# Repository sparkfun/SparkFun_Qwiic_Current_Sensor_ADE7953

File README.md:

The [SparkFun Non-Invasive Current Sensor - ADE7953 (Qwiic)](https://www.sparkfun.com/sparkfun-non-invasive-current-sensor-ade7953-qwiic.html) is a dual-channel, non-invasive current measurement breakout built around the ADE7953 energy metering IC from Analog Devices. Using inexpensive SCT-013 split-core current transformers (CT clamps), you can measure AC current on up to two channels without ever breaking a wire. The board accepts CT input through a standard 3.5mm TRRS audio jack or through the A+/A- and B+/B- terminal connections, giving you flexibility for both quick prototyping and permanent installations.

Designed for our [Qwiic ecosystem](https://www.sparkfun.com/qwiic), the ADE7953 handles all of the signal conditioning, sampling, and power calculations on-chip, delivering calibrated current readings over I2C so your host microcontroller can stay focused on application logic. Whether you are building a home energy monitor, an industrial equipment dashboard, or a smart breaker panel, this board gives you metering-grade measurements in a compact, breadboard-friendly package.

## Repository Contents

* **/docs** - Documentation files for GitHub pages
* **/Documents** - Datasheets, additional product information
* **/Hardware** - KiCad design files (.kicad_sch, .kicad_pcb)
* **/Production** - Production panel files

## Documentation

* **[Library](https://github.com/sparkfun/SparkFun_ADE7953_Arduino_Library)** - Arduino library for the SparkFun Non-Invasive Current Sensor - ADE7953 (Qwiic).
* **[Hookup Guide](https://docs.sparkfun.com/SparkFun_Qwiic_Current_Sensor_ADE7953/)** - Basic hookup guide for the SparkFun Non-Invasive Current Sensor - ADE7953 (Qwiic).

## Product Versions

* **[SEN-31409](https://www.sparkfun.com/sparkfun-non-invasive-current-sensor-ade7953-qwiic.html)** - Initial release of the SparkFun Qwiic Current Sensor - ADE7953.

## License Information

This product is _**open source**_!

Please review the LICENSE.md file for license information.

If you have any questions or concerns about licensing, please contact technical support on our [SparkFun forums](https://forum.sparkfun.com/viewforum.php?f=152).

Distributed as-is; no warranty is given.

_- Your friends at SparkFun._

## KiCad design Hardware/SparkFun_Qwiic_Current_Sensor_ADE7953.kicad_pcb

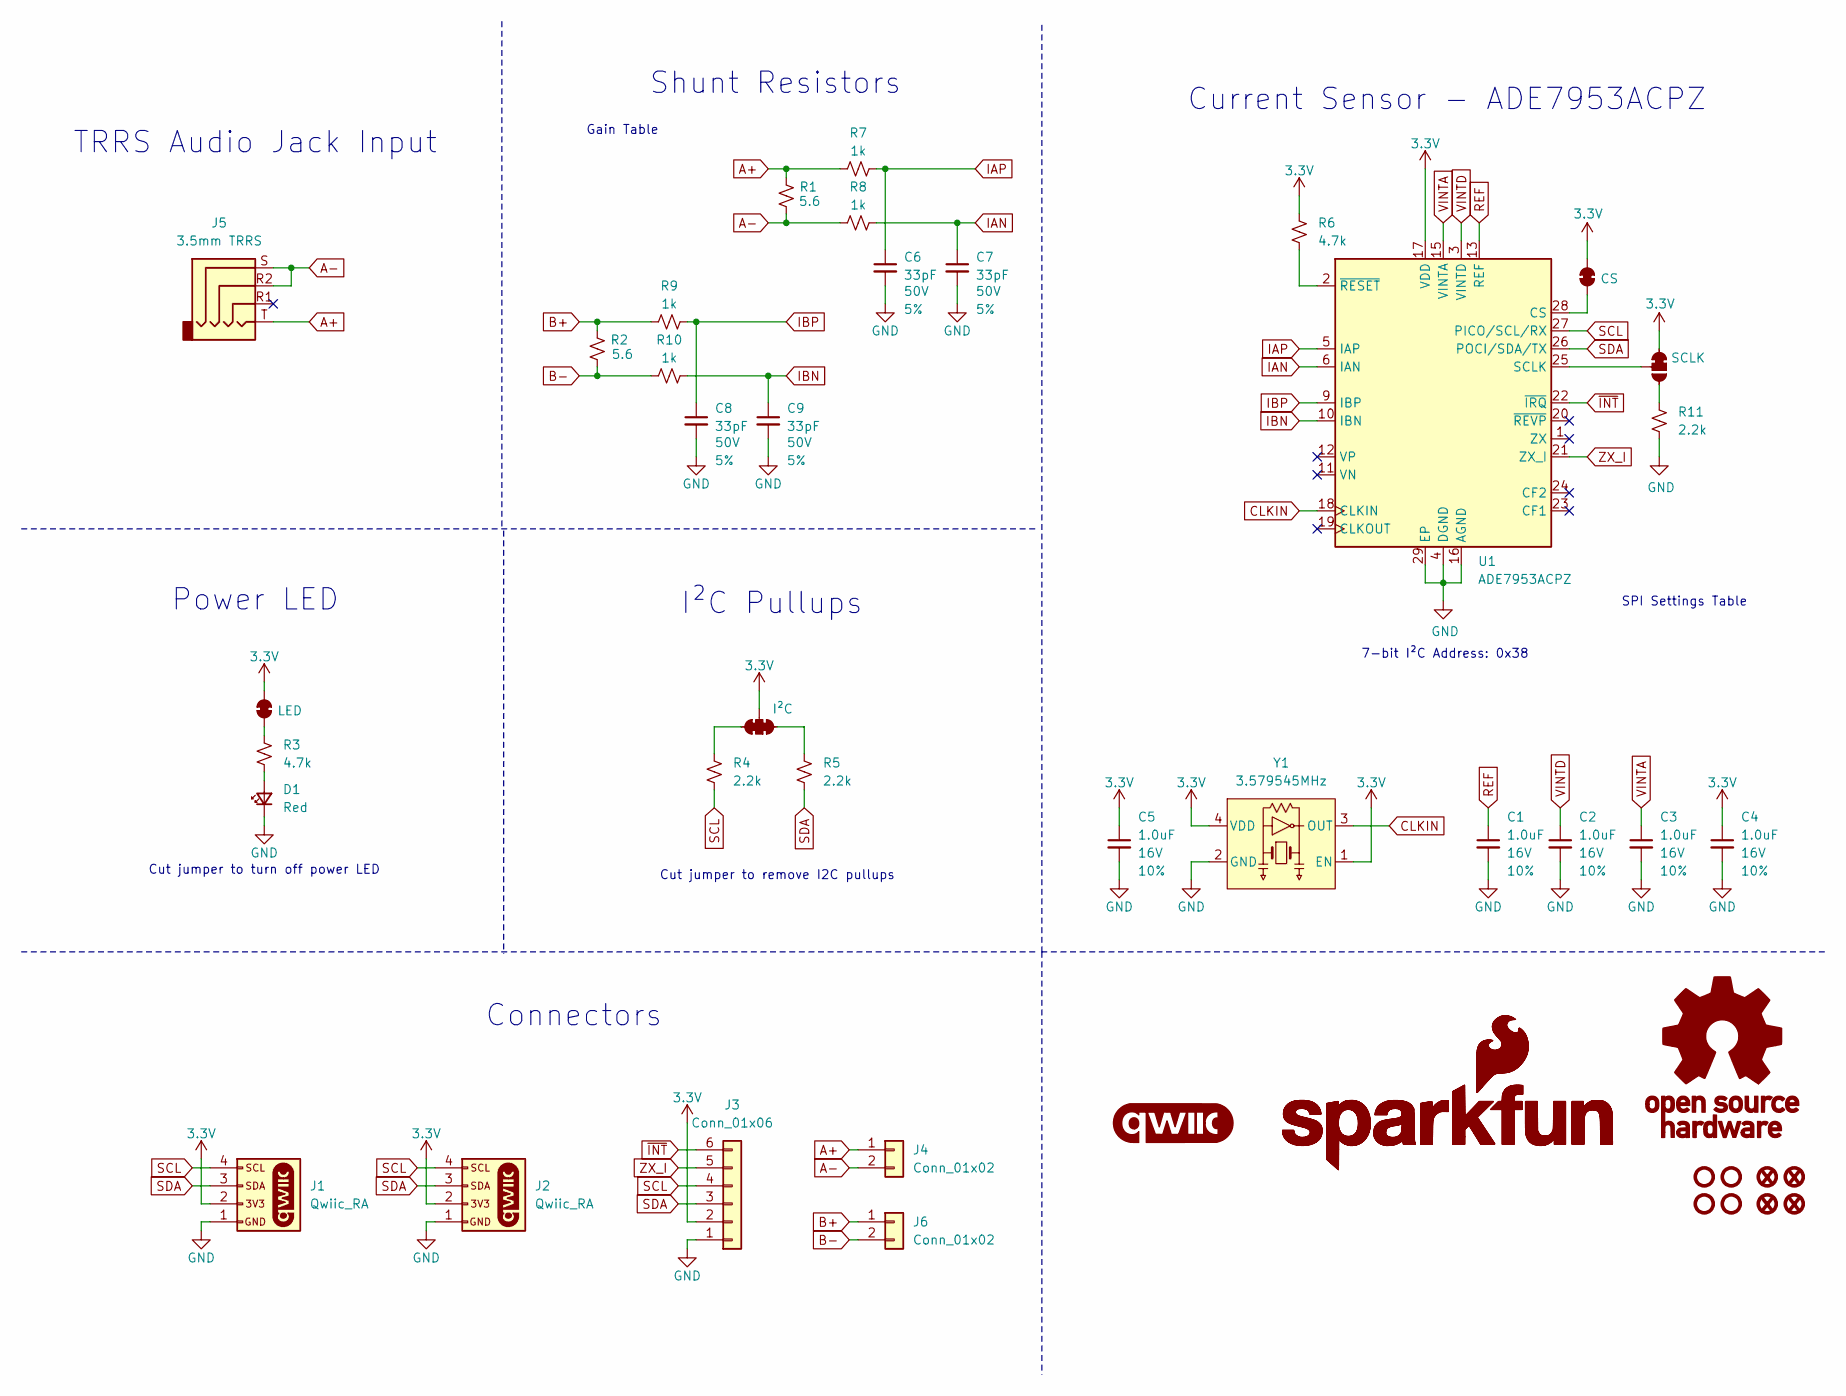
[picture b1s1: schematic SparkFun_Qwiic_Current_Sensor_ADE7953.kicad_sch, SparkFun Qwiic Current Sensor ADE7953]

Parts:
C1, C2, C3, C4, C5: 1.0uF; C_0402_1005Metric; Voltage 16V; Tolerance 10%
C6, C7, C8, C9: 33pF; C_0402_1005Metric; Voltage 50V; Tolerance 5%
D1: Red; LED_0603_1608Metric_Red
FID1, FID2, FID3, FID4: Fiducial_0.5mm; Fiducial_0.5mm_Mask1mm
G1: qwiic_Logo
G2: SparkFun_Logo; SparkFun_Logo_8mm
G3: SparkFun_Logo
G4: OSHW_Logo; Creative_Commons_License
J1, J2: Qwiic_RA; JST_1x04_P1.0mm_Horizontal_SMD
J3: Conn_01x06; 1x06_P2.54mm
J4, J6: Conn_01x02; 1x02_P2.54mm
J5: 3.5mm TRRS; Audio_Jack_3.5mm_TRRS_SMD_RA
JP1: LED; Jumper_2_NC_Trace
JP2: I²C; Jumper_3_NC-2_Trace
JP3: SCLK; Jumper_3_NC-1_Trace
JP4: CS; Jumper_2_NC_Trace
R1, R2: 5.6; R_0603_1608Metric
R3, R6: 4.7k; R_0603_1608Metric
R4, R5, R11: 2.2k; R_0402_1005Metric
R7, R8, R9, R10: 1k; R_0402_1005Metric
ST1, ST2, ST3, ST4: Standoff
U1: ADE7953ACPZ; QFN-28-1EP_4x4_5mmx5mm; Manufacturer_Part_Number ADE7953ACPZ; Mouser Part Number 584-ADE7953ACPZ
Y1: 3.579545MHz; Crystal_SMD_3.2x2.5mm

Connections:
3.3V: C4.1, C5.1, J1.2, J2.2, J3.2, JP1.2 (B), JP2.2 (B), JP3.1 (A), JP4.2 (B), R6.2, U1.7 (PULL_HIGH_1), U1.8 (PULL_HIGH_2), U1.17 (VDD), Y1.1 (EN), Y1.4 (VDD)
A+: J4.1, J5.T, R1.2, R7.1
A-: J4.2, J5.R2, J5.S, R1.1, R8.1
B+: J6.1, R2.2, R9.1
B-: J6.2, R2.1, R10.1
CLKIN: U1.18 (CLKIN), Y1.3 (OUT)
GND: C1.2, C2.2, C3.2, C4.2, C5.2, C6.2, C7.2, C8.2, C9.2, D1.1 (K), J1.1, J2.1, J3.1, R11.1, U1.4 (DGND), U1.14 (PULL_LOW), U1.16 (AGND), U1.29 (EP), Y1.2 (GND)
IAN: C7.1, R8.2, U1.6 (IAN)
IAP: C6.1, R7.2, U1.5 (IAP)
IBN: C9.1, R10.2, U1.10 (IBN)
IBP: C8.1, R9.2, U1.9 (IBP)
unnamed: D1.2 (A), R3.1
unnamed: JP1.1 (A), R3.2
unnamed: JP2.1 (A), R5.2
unnamed: JP2.3 (C), R4.2
unnamed: JP3.2 (B), U1.25 (SCLK)
unnamed: JP3.3 (C), R11.2
unnamed: JP4.1 (A), U1.28 (CS)
unnamed: R6.1, U1.2 (~RESET)
REF: C1.1, U1.13 (REF)
SCL: J1.4, J2.4, J3.4, R4.1, U1.27 (PICO/SCL/RX)
SDA: J1.3, J2.3, J3.3, R5.1, U1.26 (POCI/SDA/TX)
VINTA: C3.1, U1.15 (VINTA)
VINTD: C2.1, U1.3 (VINTD)
ZX_I: J3.5, U1.21 (ZX_I)
~INT: J3.6, U1.22 (~IRQ)

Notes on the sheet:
SPI Settings Table
Current Sensor - ADE7953ACPZ
Shunt Resistors
TRRS Audio Jack Input
7-bit I²C Address: 0x38
Cut jumper to turn off power LED
Power LED
Cut jumper to remove I2C pullups
Gain Table
Connectors
I²C Pullups

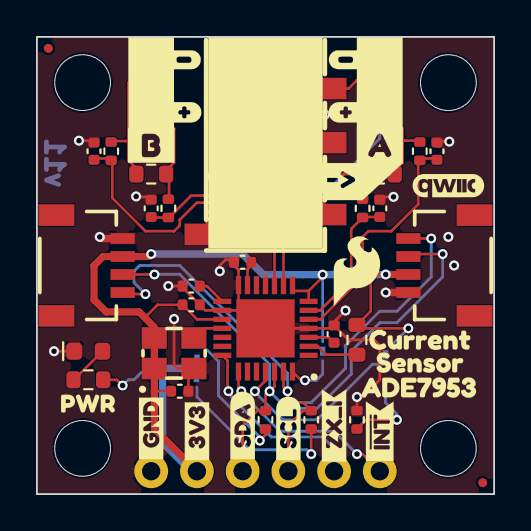
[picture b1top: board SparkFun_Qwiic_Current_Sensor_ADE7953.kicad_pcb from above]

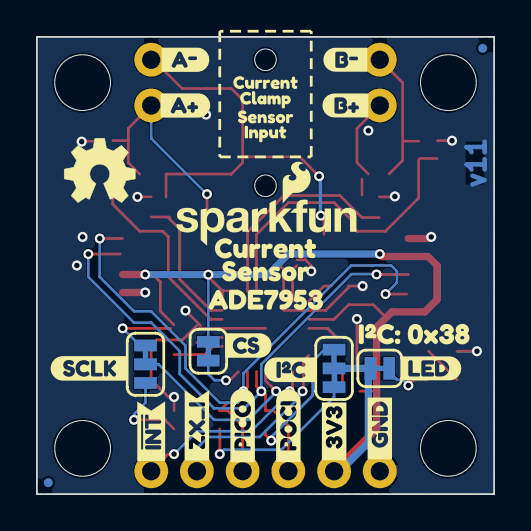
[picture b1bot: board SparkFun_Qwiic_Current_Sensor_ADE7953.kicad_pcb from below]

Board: 2 copper layers, 25.4 x 25.4 mm, 83 parts (29 on the bottom side), 26 nets.

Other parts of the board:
Ref**: Val**; OSHW_Logo_4mm
kibuzzard-6A8F671A: G***; kibuzzard-6A8F671A
kibuzzard-6A8F6918: G***; kibuzzard-6A8F6918
kibuzzard-6A8F6922: G***; kibuzzard-6A8F6922
kibuzzard-6A3051E6: G***; kibuzzard-6A3051E6
kibuzzard-69F8C340: G***; kibuzzard-69F8C340
kibuzzard-69F8FC1F, kibuzzard-69F8FC1F#2: G***; kibuzzard-69F8FC1F
kibuzzard-69F8FC56, kibuzzard-69F8FC56#2: G***; kibuzzard-69F8FC56
kibuzzard-69F8FCF4: G***; kibuzzard-69F8FCF4
kibuzzard-69F8FD80: G***; kibuzzard-69F8FD80
kibuzzard-69FA12A1, kibuzzard-69FA12A1#2: G***; kibuzzard-69FA12A1
kibuzzard-69FA12DB: G***; kibuzzard-69FA12DB
kibuzzard-69FA13A0: G***; kibuzzard-69FA13A0
kibuzzard-69FA13AB: G***; kibuzzard-69FA13AB
kibuzzard-69FA13C4: G***; kibuzzard-69FA13C4
kibuzzard-69FA13D5: G***; kibuzzard-69FA13D5
kibuzzard-69FA128B, kibuzzard-69FA128B#2: G***; kibuzzard-69FA128B
kibuzzard-69FA1293, kibuzzard-69FA1293#2: G***; kibuzzard-69FA1293
kibuzzard-69FCD097: G***; kibuzzard-69FCD097
kibuzzard-69FCDE2E: G***; kibuzzard-69FCDE2E
kibuzzard-69FD0DBC: G***; kibuzzard-69FD0DBC
kibuzzard-69FD0DD3: G***; kibuzzard-69FD0DD3
kibuzzard-69FD0DDA: G***; kibuzzard-69FD0DDA
kibuzzard-69FD0F08: G***; kibuzzard-69FD0F08
kibuzzard-69FD10A0: G***; kibuzzard-69FD10A0
kibuzzard-69FD10AE: G***; kibuzzard-69FD10AE
kibuzzard-69FD1032: G***; kibuzzard-69FD1032
kibuzzard-69FD1060: G***; kibuzzard-69FD1060
kibuzzard-689A66E2: G***; kibuzzard-689A66E2
kibuzzard-689A66E9: G***; kibuzzard-689A66E9
kibuzzard-689A66EE: G***; kibuzzard-689A66EE
kibuzzard-689A66F4: G***; kibuzzard-689A66F4
kibuzzard-689A642E: G***; kibuzzard-689A642E
kibuzzard-689A6721: G***; kibuzzard-689A6721
kibuzzard-689A6728: G***; kibuzzard-689A6728
kibuzzard-689A6796: G***; kibuzzard-689A6796

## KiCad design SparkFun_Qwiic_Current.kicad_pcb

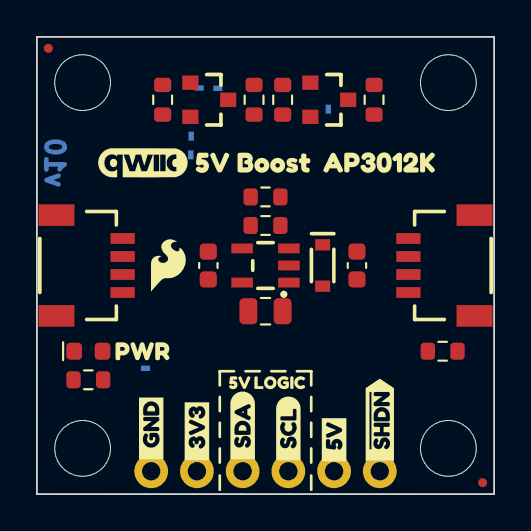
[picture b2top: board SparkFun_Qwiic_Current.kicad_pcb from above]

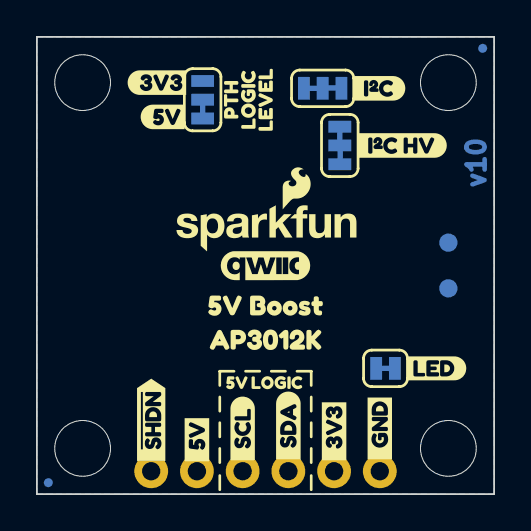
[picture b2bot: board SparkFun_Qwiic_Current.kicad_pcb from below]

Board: 2 copper layers, 25.4 x 25.4 mm, 63 parts (26 on the bottom side), 17 nets, no tracks yet.

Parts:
C1, C2: 1.0uF; C_0603_1608Metric
D1: Red; LED_0603_1608Metric_Red
D2: PMEG4005EJ; SOD-323
FID1, FID2, FID3, FID4: Fiducial_0.5mm; Fiducial_0.5mm_Mask1mm
G4: OSHW_Logo; Creative_Commons_License
J1, J2: Qwiic_RA; JST_1x04_P1.0mm_Horizontal_SMD
J3: Conn_01x06; 1x06_P2.54mm
JP1: LED; Jumper_2_NC_Trace
JP2: I2C; Jumper_3_NC-2_Trace
JP3: LOGIC; Jumper_3_NC-1_Trace
JP4: I2C HV; Jumper_3_NC-2_Trace
L1: 10uH; C_0805_2012Metric
Q1, Q2: BSS138; SOT23-3
R1, R6: 100k; R_0603_1608Metric
R2: 33k; R_0603_1608Metric
R3: 4.7k; R_0603_1608Metric
R4, R5, R7, R8: 2.2k; R_0603_1608Metric
ST1, ST2, ST3, ST4: Standoff
TP1, TP2: 1.0mm; TestPoint-1.0mm
U5: AP3012; SOT23-5
kibuzzard-689A64A8: G***; kibuzzard-689A64A8
kibuzzard-689A66E2: G***; kibuzzard-689A66E2
kibuzzard-689A66E9: G***; kibuzzard-689A66E9
kibuzzard-689A66EE: G***; kibuzzard-689A66EE
kibuzzard-689A66F4: G***; kibuzzard-689A66F4
kibuzzard-689A66F9: G***; kibuzzard-689A66F9
kibuzzard-689A66FE: G***; kibuzzard-689A66FE
kibuzzard-689A642E: G***; kibuzzard-689A642E
kibuzzard-689A644B: G***; kibuzzard-689A644B
kibuzzard-689A648B: G***; kibuzzard-689A648B
kibuzzard-689A649F: G***; kibuzzard-689A649F
kibuzzard-689A670C: G***; kibuzzard-689A670C
kibuzzard-689A676B: G***; kibuzzard-689A676B
kibuzzard-689A6411: G***; kibuzzard-689A6411
kibuzzard-689A6418: G***; kibuzzard-689A6418
kibuzzard-689A6454: G***; kibuzzard-689A6454
kibuzzard-689A6479: G***; kibuzzard-689A6479
kibuzzard-689A6481: G***; kibuzzard-689A6481
kibuzzard-689A6494: G***; kibuzzard-689A6494
kibuzzard-689A6706: G***; kibuzzard-689A6706
kibuzzard-689A6711: G***; kibuzzard-689A6711
kibuzzard-689A6718: G***; kibuzzard-689A6718
kibuzzard-689A6721: G***; kibuzzard-689A6721
kibuzzard-689A6728: G***; kibuzzard-689A6728
kibuzzard-689A6759: G***; kibuzzard-689A6759
kibuzzard-689A6762: G***; kibuzzard-689A6762
kibuzzard-689A6771: G***; kibuzzard-689A6771
kibuzzard-689A6775: G***; kibuzzard-689A6775
kibuzzard-689A6796: G***; kibuzzard-689A6796

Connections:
3.3V: C1.1, J1.2, J2.2, J3.2, JP1.2 (B), JP2.2 (B), JP3.3 (C), L1.1, Q1.1 (G), Q2.1 (G), R6.2, U5.5 (IN)
5V: C2.1, D2.1 (K), J3.5, JP3.1 (A), R1.2
GND: C1.2, C2.2, D1.1 (K), J1.1, J2.1, J3.1, R2.2, U5.2 (GND)
HV_SCL: J3.4, Q1.3 (D), R8.2
HV_SDA: J3.3, Q2.3 (D), R7.2
unnamed: D1.2 (A), R3.1
unnamed: D2.2 (A), L1.2, U5.1 (SW)
unnamed: JP1.1 (A), R3.2
unnamed: JP2.1 (A), R5.1
unnamed: JP2.3 (C), R4.2
unnamed: JP4.1 (A), R7.1
unnamed: JP4.3 (C), R8.1
unnamed: R1.1, R2.1, U5.3 (FB)
SCL: J1.4, J2.4, Q1.2 (S), R5.2, TP2.1
SDA: J1.3, J2.3, Q2.2 (S), R4.1, TP1.1
VCC: JP3.2 (B), JP4.2 (B)
~SHDN: J3.6, R6.1, U5.4 (~SHDN)

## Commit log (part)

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2026-05-04 Re-arranged File Structure to match standard
2026-05-04 Updated PCB and Schematic
2026-05-04 Updated IC Schematic Symbols
2026-05-04 Updated PCB Layout
2026-05-05 Added silkscreen and minor alignment fixes
2026-05-05 Added XTAL Osc.
2026-05-05 Added XTAL Datasheet, Renamed folder to Documents
2026-05-05 Fixed Reset Pin and Shunt Resistors
2026-05-08 Implemented changes after design review
2026-05-08 Moved R11
2026-05-08 Updated part libraries
2026-05-08 Add Gerbers
2026-05-08 Replaced 4x4mm with 5x5mm footprint
2026-05-08 Updated a few vias
2026-05-11 Changed 4x4 chip size to 5x5mm
2026-06-15 Updated number for Reds, added I2C Addr
2026-06-18 Updated PCB based on Design Review II feedback
    - Updated schematic I2C labels
    - Updated component silkscreens and courtyards
2026-06-22 Fixed 8mil traces -> 6mil traces

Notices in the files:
parts and their libraries:
Released under the Creative Commons Attribution Share-Alike 4.0 License
https://creativecommons.org/licenses/by-sa/4.0
